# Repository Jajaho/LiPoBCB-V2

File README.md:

# LiPoBCB-V2
LiPo Battery Charger Booster V2

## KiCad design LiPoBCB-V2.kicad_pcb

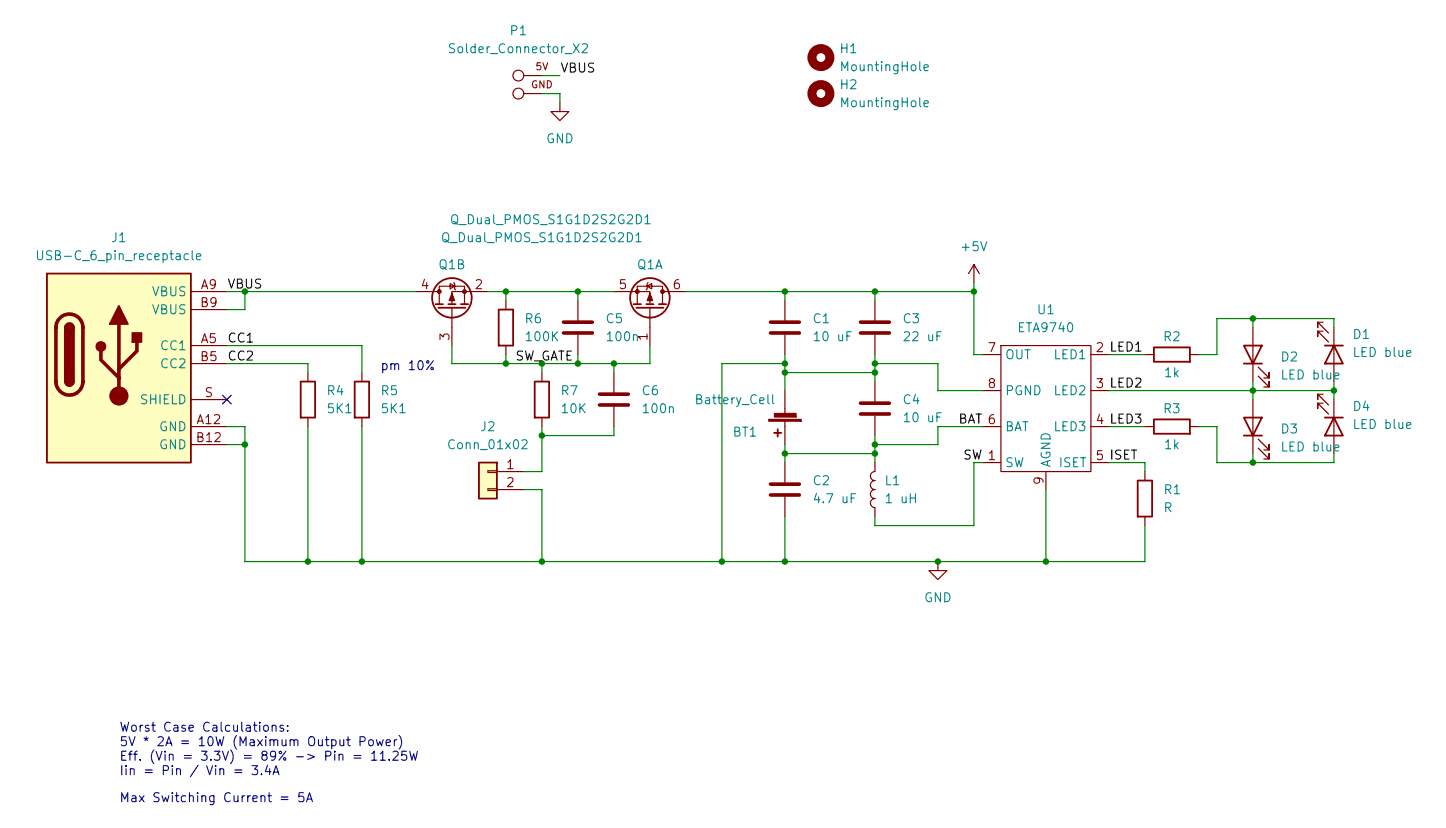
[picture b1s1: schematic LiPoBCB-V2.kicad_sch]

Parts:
BT1: Battery_Cell; JST_PH_B2B-PH-K_1x02_P2.00mm_Vertical
C1, C4: 10 uF; C_0603_1608Metric
C2: 4.7 uF; C_0603_1608Metric
C3: 22 uF; C_0805_2012Metric
C5, C6: 100n; C_0603_1608Metric
D1, D2, D3, D4: LED blue; D_0603_1608Metric
H1, H2: MountingHole; MountingHole_2.2mm_M2_ISO14580
J1: USB-C_6_pin_receptacle; Korean Hroparts Elec TYPE-C-31-M-17
J2: Conn_01x02; Solder_Connector_SW
L1: 1 uH; L_smd_1616
P1: Solder_Connector_X2
Q1: Q_Dual_PMOS_S1G1D2S2G2D1; SOT-23-6
R1: R; R_0603_1608Metric
R2, R3: 1k; R_0603_1608Metric
R4, R5: 5K1; R_0603_1608Metric
R6: 100K; R_0603_1608Metric
R7: 10K; R_0603_1608Metric
U1: ETA9740; SOIC-8-1EP_3.9x4.9mm_P1.27mm_EP2.29x3mm

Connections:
+5V: C1.1, C3.1, Q1.6 (D), U1.7 (OUT)
/BAT: BT1.1 (+), C2.1, C4.2, L1.2, U1.6 (BAT)
/CC1: J1.A5 (CC1), R5.1
/CC2: J1.B5 (CC2), R4.1
/ISET: R1.1, U1.5 (ISET)
/LED1: R2.1, U1.2 (LED1)
/LED2: D1.2 (A), D2.1 (K), D3.2 (A), D4.1 (K), U1.3 (LED2)
/LED3: R3.1, U1.4 (LED3)
/SW: L1.1, U1.1 (SW)
/SW_GATE: C5.2, C6.1, Q1.1 (G), Q1.3 (G), R6.2, R7.1
/VBUS: J1.A9 (VBUS), J1.B9 (VBUS), P1.1 (5V), Q1.4 (D)
GND: BT1.2 (-), C1.2, C2.2, C3.2, C4.1, J1.A12 (GND), J1.B12 (GND), J2.2, P1.2 (GND), R1.2, R4.2, R5.2, U1.8 (PGND), U1.9 (AGND)
unnamed: C5.1, Q1.2 (S), Q1.5 (S), R6.1
unnamed: C6.2, J2.1, R7.2
unnamed: D1.1 (K), D2.2 (A), R2.2
unnamed: D3.1 (K), D4.2 (A), R3.2

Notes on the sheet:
Worst Case Calculations: 5V * 2A = 10W (Maximum Output Power) Eff. (Vin = 3.3V) = 89% -> Pin = 11.25W Iin = Pin / Vin = 3.4A
pm 10%
Max Switching Current = 5A

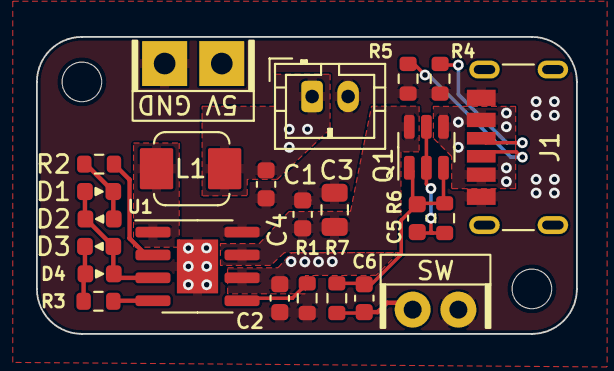
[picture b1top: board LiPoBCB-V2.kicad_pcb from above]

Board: 2 copper layers, 30.0 x 16.5 mm, 26 parts (0 on the bottom side), 16 nets.

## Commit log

2022-11-29 project setup
2022-11-29 started schematic
2022-11-29 added usb-c port
2022-11-29 added fets
2022-11-29 replaced usb-c port
2022-12-01 created board outline
2022-12-01 first routing test
2022-12-01 added jlcpcb drc
    fixed edge outline
2022-12-01 added polygons
2022-12-02 moved pcb, redefined edge
2022-12-02 moved top polygons
2022-12-03 DRC no errors
    added 3d models
    switched q1a and q1b
    optimized polygons
2022-12-03 Updates design rules
    edited inductor footprint
    removed custom design rules
2022-12-03 Adds new solder connector footprints
2022-12-03 Adds silkscreen to the back
2022-12-03 Changes Netclass clearance from 0,2 mm to 0,127 mm
